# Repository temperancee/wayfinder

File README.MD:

# Wayfinder

A quadcopter flight computer built using a custom PCB with a XIAO ESP32S3 Sense daughter board.

Software written in C and Arudino, using the Espressif-IDF version of FreeRTOS. Implements a Kalman Filter and (todo) a PID loop.

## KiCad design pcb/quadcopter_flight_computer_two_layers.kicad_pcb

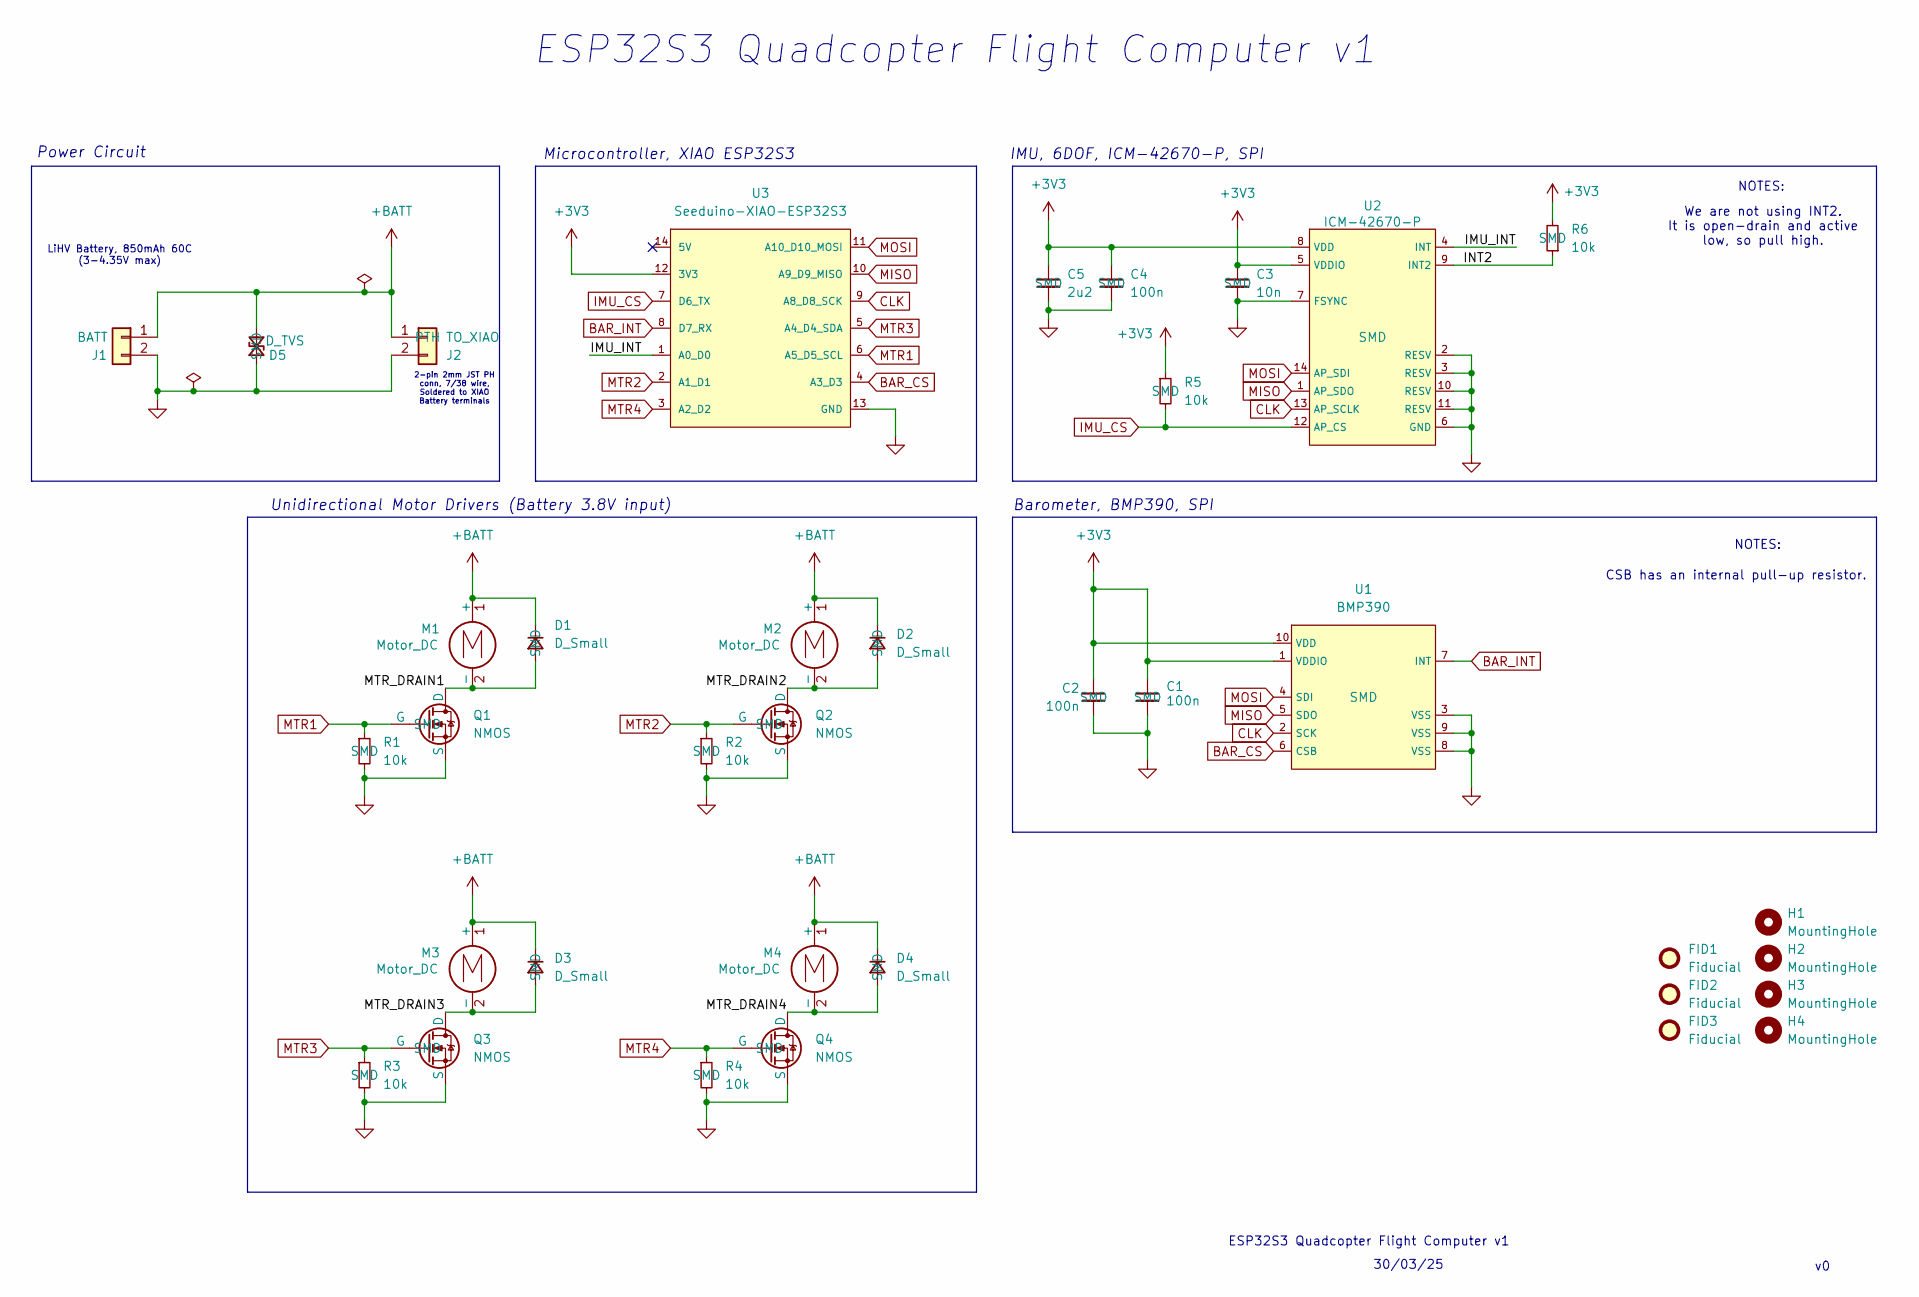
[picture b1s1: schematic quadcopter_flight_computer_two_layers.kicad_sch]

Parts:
C1, C2: 100n; C_0603_1608Metric; Manufacturer Part No. CL10B104KA8NNNC
C3: 10n; C_0402_1005Metric; Manufacturer Part No. CL05B103KB5NNNC
C4: 100n; C_0402_1005Metric; Manufacturer Part No. CL05B104KP5NNNC
C5: 2u2; C_0603_1608Metric; Manufacturer Part No. CL10B225KP8NNNC
D1, D2, D3, D4: D_Small; D_SOD-123; Manufacturer Part No. 1N4148W-7-F
D5: D_TVS; D_SMA; Manufacturer Part No. SMAJ5.0CA
FID1, FID2, FID3: Fiducial; Fiducial_1mm_Mask2mm
H1, H2, H3, H4: MountingHole; MountingHole_2.2mm_M2_DIN965
J1: BATT; 1S LiPo Battery
J2: TO_XIAO; JST_PH_B2B-PH-K_1x02_P2.00mm_Vertical; Manufacturer Part No. B2B-PH-K-S
M1, M2, M3, M4: Motor_DC; 8520_Coreless_Motor
Q1, Q2, Q3, Q4: NMOS; DMN1019USN; Manufacturer Part No. DMN1019USN-13
R1, R2, R3, R4: 10k; R_0603_1608Metric; Manufacturer Part No. RC1608F103CS
R5, R6: 10k; R_0402_1005Metric; Manufacturer Part No. RC1005F103CS
U1: BMP390; Manufacturer Part No. BMP390
U2: ICM-42670-P; Manufacturer Part No. ICM-42670-P
U3: Seeduino-XIAO-ESP32S3; XIAO-ESP32S3-THT

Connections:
+3V3: C1.1, C2.1, C3.1, C4.1, C5.1, R5.1, R6.2, U1.1 (VDDIO), U1.10 (VDD), U2.5 (VDDIO), U2.8 (VDD), U3.12 (3V3)
+BATT: D1.1 (K), D2.1 (K), D3.1 (K), D4.1 (K), D5.2 (A2), J1.1, J2.1, M1.1 (+), M2.1 (+), M3.1 (+), M4.1 (+)
/IMU_INT: U2.4 (INT), U3.1 (A0_D0)
/INT2: R6.1, U2.9 (INT2)
/MTR_DRAIN1: D1.2 (A), M1.2 (-), Q1.1 (D)
/MTR_DRAIN2: D2.2 (A), M2.2 (-), Q2.1 (D)
/MTR_DRAIN3: D3.2 (A), M3.2 (-), Q3.1 (D)
/MTR_DRAIN4: D4.2 (A), M4.2 (-), Q4.1 (D)
BAR_CS: U1.6 (CSB), U3.4 (A3_D3)
BAR_INT: U1.7 (INT), U3.8 (D7_RX)
CLK: U1.2 (SCK), U2.13 (AP_SCLK), U3.9 (A8_D8_SCK)
GND: C1.2, C2.2, C3.2, C4.2, C5.2, D5.1 (A1), J1.2, J2.2, Q1.3 (S), Q2.3 (S), Q3.3 (S), Q4.3 (S), R1.2, R2.2, R3.2, R4.2, U1.3 (VSS), U1.8 (VSS), U1.9 (VSS), U2.2 (RESV), U2.3 (RESV), U2.6 (GND), U2.7 (FSYNC), U2.10 (RESV), U2.11 (RESV), U3.13 (GND)
IMU_CS: R5.2, U2.12 (AP_CS), U3.7 (D6_TX)
MISO: U1.5 (SDO), U2.1 (AP_SDO), U3.10 (A9_D9_MISO)
MOSI: U1.4 (SDI), U2.14 (AP_SDI), U3.11 (A10_D10_MOSI)
MTR1: Q1.2 (G), R1.1, U3.6 (A5_D5_SCL)
MTR2: Q2.2 (G), R2.1, U3.2 (A1_D1)
MTR3: Q3.2 (G), R3.1, U3.5 (A4_D4_SDA)
MTR4: Q4.2 (G), R4.1, U3.3 (A2_D2)

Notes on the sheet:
Microcontroller, XIAO ESP32S3
Unidirectional Motor Drivers (Battery 3.8V input)
IMU, 6DOF, ICM-42670-P, SPI
LiHV Battery, 850mAh 60C (3-4.35V max)
We are not using INT2. It is open-drain and active low, so pull high.
NOTES:
ESP32S3 Quadcopter Flight Computer v1
CSB has an internal pull-up resistor.
2-pin 2mm JST PH conn, 7/38 wire, Soldered to XIAO Battery terminals
Power Circuit
30/03/25
Barometer, BMP390, SPI

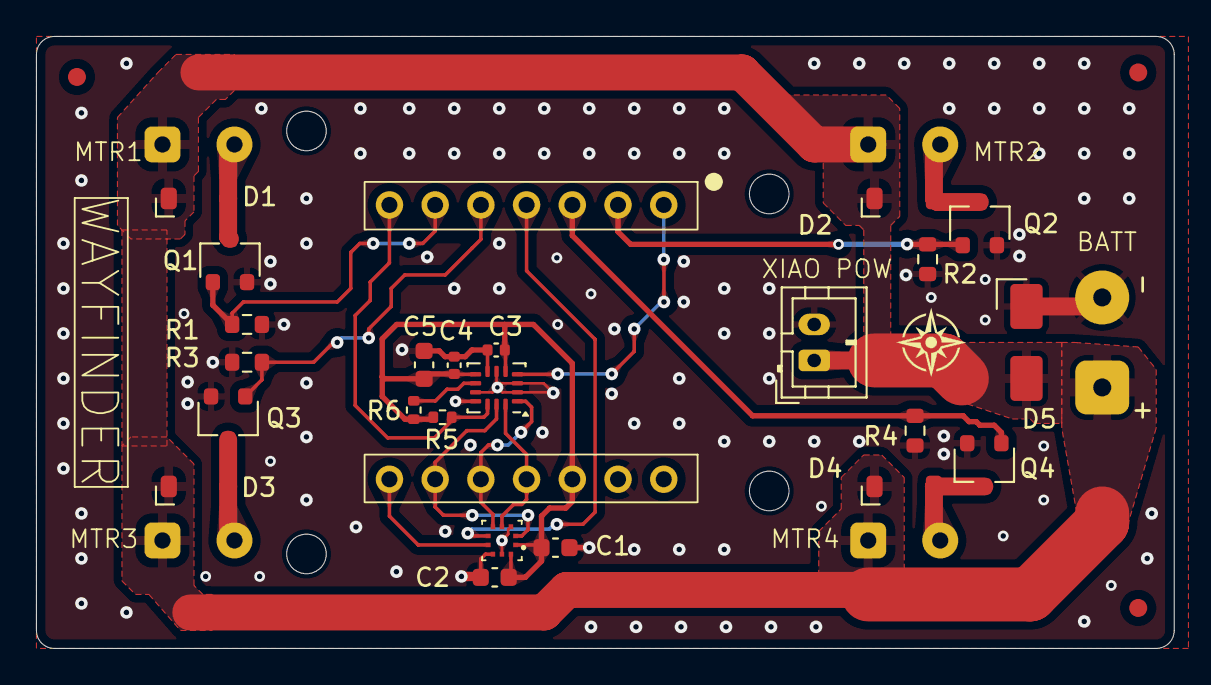
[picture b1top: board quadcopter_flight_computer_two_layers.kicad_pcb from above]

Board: 2 copper layers, 63.2 x 34.0 mm, 36 parts (0 on the bottom side), 19 nets.

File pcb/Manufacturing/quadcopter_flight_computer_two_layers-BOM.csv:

"Reference","Value","Footprint","Qty","Description","Distributor Link","Manufacturer","Manufacturer Part No.","Type"
"C1,C2","100n","Capacitor_SMD:C_0603_1608Metric","2","Unpolarized capacitor, small symbol","https://www.digikey.co.uk/en/products/detail/samsung-electro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","Samsung Electro-Mechanics","CL10B104KA8NNNC","SMD"
"C3","10n","Capacitor_SMD:C_0402_1005Metric","1","Unpolarized capacitor, small symbol","https://www.digikey.co.uk/en/products/detail/samsung-electro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","Samsung Electro-Mechanics","CL05B103KB5NNNC","SMD"
"C4","100n","Capacitor_SMD:C_0402_1005Metric","1","Unpolarized capacitor, small symbol","https://www.digikey.co.uk/en/products/detail/samsung-electro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","Samsung Electro-Mechanics","CL05B104KP5NNNC","SMD"
"C5","2u2","Capacitor_SMD:C_0603_1608Metric","1","Unpolarized capacitor, small symbol","https://www.digikey.co.uk/en/products/detail/samsung-electro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","Samsung Electro-Mechanics","CL10B225KP8NNNC","SMD"
"D1,D2,D3,D4","D_Small","My_Diode_SMD:D_SOD-123","4","Diode, small symbol","https://www.digikey.co.uk/en/products/detail/diodes-incorpor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","Diodes Incorporated","1N4148W-7-F","SMD"
"D5","D_TVS","My_Diode_SMD:D_SMA","1","Bidirectional transient-voltage-suppression diode, small symbol","https://www.digikey.co.uk/en/products/detail/bourns-inc/SMAJ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","Bourns Inc.","SMAJ5.0CA","SMD"
"J2","TO_XIAO","Connector_JST:JST_PH_B2B-PH-K_1x02_P2.00mm_Vertical","1","Generic connector, single row, 01x02, script generated (kicad-library-utils/schlib/autogen/connector/)","https://www.digikey.co.uk/en/products/detail/jst-sales-ameri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","JST Sales America Inc.","B2B-PH-K-S","PTH"
"Q1,Q2,Q3,Q4","NMOS","MOSFET:DMN1019USN","4","N-MOSFET transistor, drain/source/gate","https://www.digikey.co.uk/en/products/detail/diodes-incorpor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","Diodes Incorporated","DMN1019USN-13","SMD"
"R1,R2,R3,R4","10k","Resistor_SMD:R_0603_1608Metric","4","Resistor, small symbol","https://www.digikey.co.uk/en/products/detail/samsung-electro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","Samsung Electro-Mechanics","RC1608F103CS","SMD"
"R5,R6","10k","Resistor_SMD:R_0402_1005Metric","2","Resistor, small symbol","https://www.digikey.co.uk/en/products/detail/samsung-electro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","Samsung Electro-Mechanics","RC1005F103CS","SMD"
"U1","BMP390","Barometer:BMP390","1","BMP390 Digital pressure sensor","https://www.digikey.co.uk/en/products/detail/bosch-sensortec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","Bosch Sensortec","BMP390","SMD"
"U2","ICM-42670-P","IMU:ICM-42670-P","1","ICM-42670-P 6-DOF","https://www.digikey.co.uk/en/products/detail/tdk-invensense/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","TDK InvenSense","ICM-42670-P","SMD"

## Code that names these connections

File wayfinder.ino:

// Use only core 1 because I don't know how to use multicores yet
#if CONFIG_FREERTOS_UNICORE
  static const BaseType_t app_cpu = 0;
#else
  static const BaseType_t app_cpu = 1;
#endif

#include "icm_42670_p.h"
#include <math.h>


/***************************
 * DEFINITIONS AND GLOBALS *
 ***************************/

/* Define pins */
const uint8_t INT_PIN = D0;
const uint8_t CS_PIN = D6;
const uint8_t MTR1_PIN = D5;
const uint8_t MTR2_PIN = D1;
const uint8_t MTR3_PIN = D4;
const uint8_t MTR4_PIN = D2;
// Kalman Filter
#define t 2.0f              // Kalman filter predict time step in ms
#define MEASURE_TIME 10.0f      // Kalman filter measurement time step in ms
#define SIGMA_INIT 0.01f    // Initial values on diagonal of sigma (i.e. initial roll and pitch variances)
#define R_INIT 0.001f       // Initial values on diagonal of R (process noise)
#define Q_INIT 0.011f       // Initial values on diagonal of Q (measurement noise)

#define RAD_TO_DEG 57.2957795131f

/* Typedefs */
// Kalman Filter state and variance - initial state estimate is that roll and pitch are 0, as the drone will be lay flat.
typedef struct KalmanFilter {
    float roll;
    float pitch;
    float Sigma[4]; // Store as 4-dim array rather than 2x2 nested array for simplicity - 0 = 11, 1 = 12, 2 = 21, 3 = 22
    float R[2];     // R and Q are always diagonal matrices, so only store diagonal values - 0 = 11, 1 = 22
    float Q[2];
    SemaphoreHandle_t mutex;
} kalman_t;

/* Declare global objects */
icm_42670_p icm;
kalman_t kf;

// Task handles for timer callbacks
static TaskHandle_t predict_handle = NULL;
static TaskHandle_t measurement_handle = NULL;
static TimerHandle_t predict_timer = NULL;
static TimerHandle_t measurement_timer = NULL;

/***************************
 *        FUNCTIONS        *
 ***************************/

float sqr(float x)
{
    return x*x;
}



/***************************
 *        Callbacks        *
 ***************************/

void kf_timer_callback(TimerHandle_t timer_handle)
{
    // This flag compares the priority of the task woken by the notification and the task
    // that was running before the ISR and runs the higher priority one accordingly
    BaseType_t higher_priority_task_woken = pdFALSE;

    // Check predict handle is not NULL - it shouldn't be, as we assign it in setup()
    configASSERT( predict_handle != NULL );

    // Send task notification to run predict/measurement step of Kalman Filter
    if (timer_handle == predict_timer) {
        vTaskNotifyGiveFromISR(predict_handle, &higher_priority_task_woken);
    } else {
        vTaskNotifyGiveFromISR(measurement_handle, &higher_priority_task_woken);
    }
    

    // Run the higher priority task
    if (higher_priority_task_woken) {
        portYIELD_FROM_ISR();
    }
}

/***************************
 *          TASKS          *
 ***************************/

/* Kalman Filter prediction step */
void predict_task(void *arg)
{

    while (1) {

        // Run on timer interrupt - notification acts as binary semaphore
        if (ulTaskNotifyTake(pdTRUE, portMAX_DELAY) == 1) {

            // Read the data
            read_sensor_data(&icm);

            // Protect kf and icm objects with mutex
            if ( (xSemaphoreTake(kf.mutex, portMAX_DELAY) == pdTRUE) && (xSemaphoreTake(icm.mutex, portMAX_DELAY) == pdTRUE) ) {
                // Predict step
                kf.roll += (t/1000.0)*icm.gyro[0];
                kf.pitch += (t/1000.0)*icm.gyro[1];

                kf.Sigma[0] += kf.R[0];   // See formulae in obsidian notes
                kf.Sigma[3] += kf.R[1];

                xSemaphoreGive(kf.mutex);
                xSemaphoreGive(icm.mutex);
            }
            
        }
    
    }
}

/* Kalman Filter measurement step*/
void measurement_task(void *arg)
{
    // Roll and pitch angles as measured by the accelerometer
    float m_roll;
    float m_pitch;
    // Kalman gain
    float k_gain[4]; // Stored as a 1D array, just like Sigma
    float k_det;    // Determinant used in Kalman Gain calculation

    while (1) {

        // Run on timer interrupt - notification acts as binary semaphore
        if (ulTaskNotifyTake(pdTRUE, portMAX_DELAY) == 1) {

            // Read the data
            read_sensor_data(&icm);

            // Protect icm object with mutex
            if (xSemaphoreTake(icm.mutex, portMAX_DELAY) == pdTRUE) {
                // Initially, icm.accel values are 0. If this runs before the first data_ready interrupt comes in, m_roll and pitch will be NaN due to div by 0
                if (icm.accel[0] == 0) {
                    m_roll = 0;
                    m_pitch = 0;
                } else {
                    m_roll = atan( icm.accel[1] / sqrt( sqr(icm.accel[0]) + sqr(icm.accel[2]) ))*RAD_TO_DEG;
                    m_pitch = atan( -icm.accel[0] / sqrt( sqr(icm.accel[1]) + sqr(icm.accel[2]) ))*RAD_TO_DEG;
                }
                
                xSemaphoreGive(icm.mutex);
            }
            // Protect kf object with mutex
            if (xSemaphoreTake(kf.mutex, portMAX_DELAY) == pdTRUE) {

                // Kalman Gain
                k_det = 1 / ( (kf.Sigma[0]+kf.Q[0])*(kf.Sigma[3]+kf.Q[1]) - kf.Sigma[1]*kf.Sigma[2] );
                k_gain[0] = k_det * ( kf.Sigma[0]*(kf.Sigma[3] + kf.Q[1]) - kf.Sigma[1]*kf.Sigma[2] );
                k_gain[1] = k_det * ( kf.Sigma[1]*kf.Q[0] );
                k_gain[2] = k_det * ( kf.Sigma[2]*kf.Q[1] );
                k_gain[3] = k_det * ( kf.Sigma[3]*(kf.Sigma[0] + kf.Q[0]) - kf.Sigma[1]*kf.Sigma[2] );


                // State vector
                kf.roll += k_gain[0]*(m_roll - kf.roll) + k_gain[1]*(m_pitch - kf.pitch);
                kf.pitch += k_gain[2]*(m_roll - kf.roll) + k_gain[3]*(m_pitch - kf.pitch);

                // State variance
                kf.Sigma[0] = kf.Sigma[0]*(1 - k_gain[0]) + k_gain[1]*kf.Sigma[2];
                kf.Sigma[1] = kf.Sigma[1]*(1 - k_gain[0]) + k_gain[1]*kf.Sigma[3];
                kf.Sigma[2] = kf.Sigma[2]*(1 - k_gain[3]) + k_gain[2]*kf.Sigma[0];
                kf.Sigma[3] = kf.Sigma[3]*(1 - k_gain[3]) + k_gain[2]*kf.Sigma[1];

                xSemaphoreGive(kf.mutex);
            }

        }
        
    }
}

/* Prints to serial port */
void print_task(void *arg)
{

    uint8_t buf[1];


    while (1) {
        // Lock with mutex
        if (xSemaphoreTake(kf.mutex, portMAX_DELAY) == pdTRUE) { 
            Serial.print("Roll = ");
            Serial.print(kf.roll);
            Serial.print(" deg, ");
            Serial.print("Pitch = ");
            Serial.print(kf.pitch);
            Serial.println(" deg");
            Serial.println("---------------------------");

            xSemaphoreGive(kf.mutex);

            vTaskDelay(200 / portTICK_PERIOD_MS);
        }       
    }
}



/***************************
 *          SETUP          *
 ***************************/

void setup() 
{
    Serial.begin(115200);
    // Provide time for Serial to start up
    vTaskDelay(1000 / portTICK_PERIOD_MS);
    Serial.println();
    Serial.println("--- Begin ---");

    // Initialise ICM
    if (icm_initialise(&icm, CS_PIN) == -1) {
        Serial.println("ICM initialisation failed!!");
    }
      
    // Initialise KF 
    kf.mutex = xSemaphoreCreateMutex();
    kf.Sigma[0] = kf.Sigma[3] = SIGMA_INIT;
    kf.Sigma[1] = kf.Sigma[2] = 0;
    kf.R[0] = kf.R[1] = R_INIT;
    kf.Q[0] = kf.Q[1] = Q_INIT;

    // Create timer
    predict_timer = xTimerCreate("Predict Timer", t / portTICK_PERIOD_MS, pdTRUE, (void *)0, kf_timer_callback);
    measurement_timer = xTimerCreate("Measurement Timer", MEASURE_TIME / portTICK_PERIOD_MS, pdTRUE, (void *)1, kf_timer_callback);

    // Start tasks
    xTaskCreatePinnedToCore(predict_task, "predict_task", 2048, NULL, 2, &predict_handle, app_cpu);
    xTaskCreatePinnedToCore(measurement_task, "measurement_task", 2048, NULL, 2, &measurement_handle, app_cpu);
    xTaskCreatePinnedToCore(print_task, "print_task", 2048, NULL, 1, NULL, app_cpu);

    // Start timer
    configASSERT(predict_timer != NULL);
    xTimerStart(predict_timer, portMAX_DELAY);
    configASSERT(measurement_timer != NULL);
    xTimerStart(measurement_timer, portMAX_DELAY);

    // Delete setup and loop tasks
    vTaskDelete(NULL);
}

void loop() 
{
    // Execution should never reach here
}

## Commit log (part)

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2025-07-04 Added README.md
2025-07-04 Kalman Filter (no interrupt ver.) working
2025-07-05 Added PID loops
2025-11-30 Added KiCAD PCB files
